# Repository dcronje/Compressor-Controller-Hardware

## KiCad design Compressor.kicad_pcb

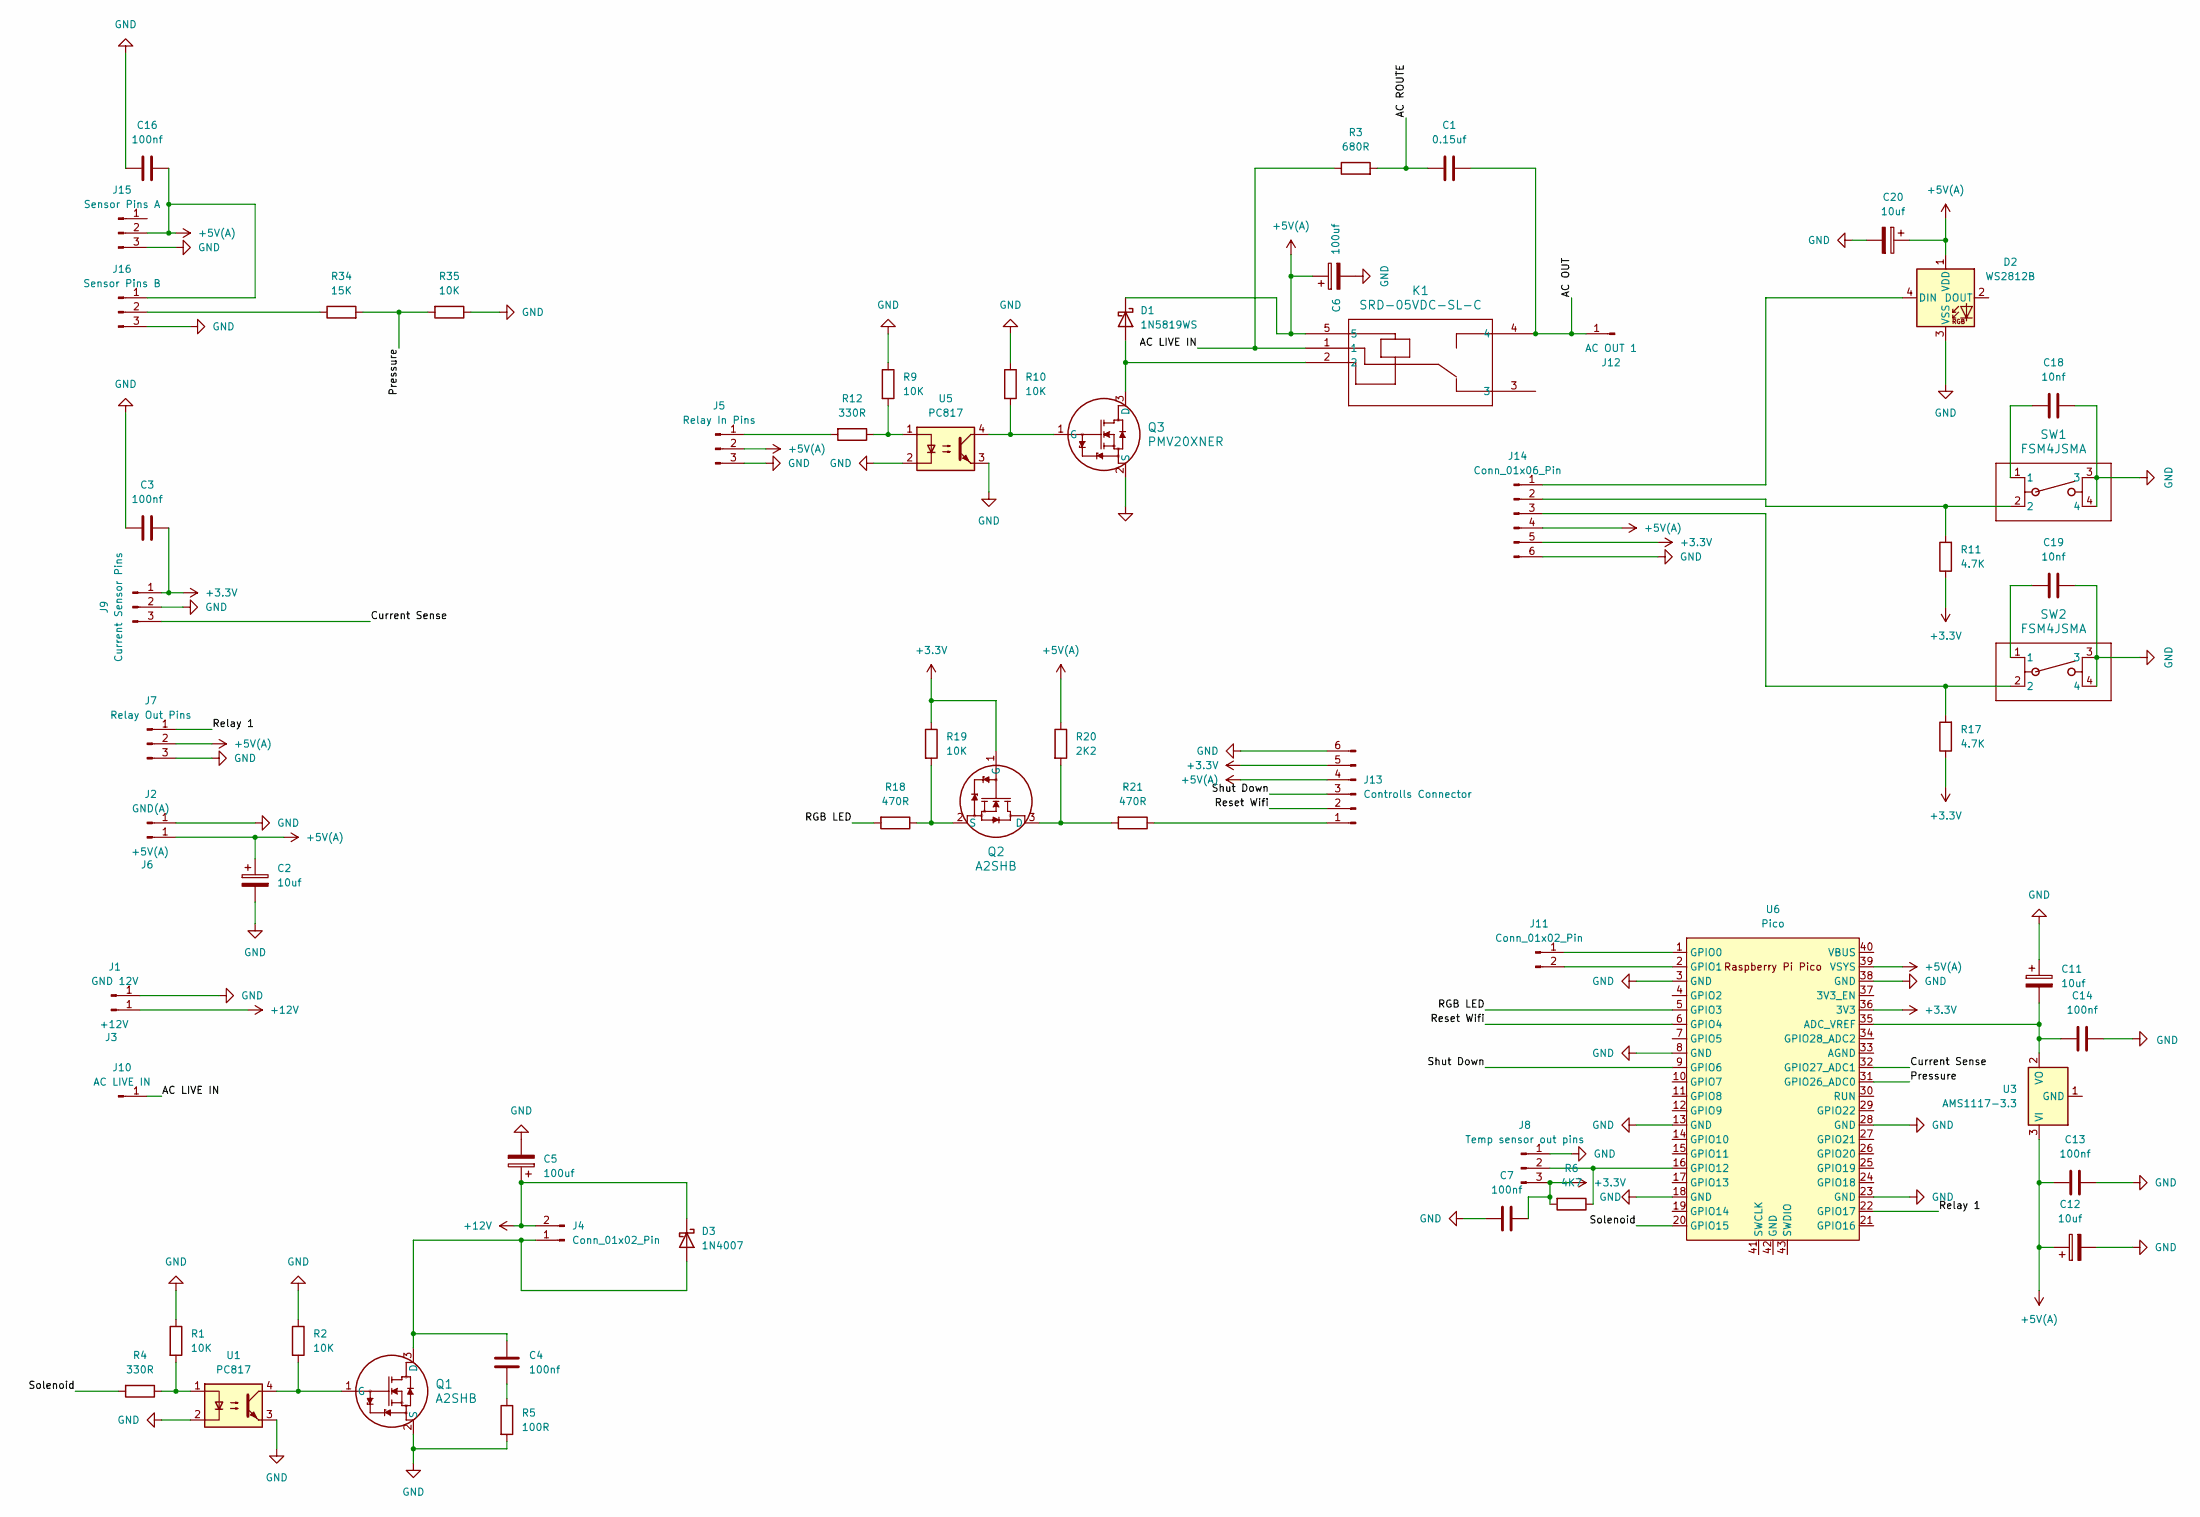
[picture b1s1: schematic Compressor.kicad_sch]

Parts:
C1: 0.15uf; C_Rect_L16.5mm_W7.0mm_P15.00mm_MKT
C2, C11, C12, C20: 10uf; CP_Elec_4x5.4
C3, C4, C7, C13, C14, C16: 100nf; C_1206_3216Metric_Pad1.33x1.80mm_HandSolder
C5, C6: 100uf; CP_Elec_10x10.5
C18, C19: 10nf; C_1206_3216Metric_Pad1.33x1.80mm_HandSolder
D1: 1N5819WS; D_SOD-323
D2: WS2812B; LED_WS2812B_PLCC4_5.0x5.0mm_P3.2mm
D3: 1N4007; D_SMA
J1: GND 12V; SolderWirePad_1x01_SMD_5x10mm
J2: GND(A); SolderWirePad_1x01_SMD_5x10mm
J3: +12V; SolderWirePad_1x01_SMD_5x10mm
J4, J11: Conn_01x02_Pin; SMD-PinHeader_1x02_P2.54mm_Vertical
J5: Relay In Pins; SMD-PinHeader_1x03_P2.54mm_Vertical
J6: +5V(A); SolderWirePad_1x01_SMD_5x10mm
J7: Relay Out Pins; SMD-PinHeader_1x03_P2.54mm_Vertical
J8: Temp sensor out pins; SMD-PinHeader_1x03_P2.54mm_Vertical
J9: Current Sensor Pins; SMD-PinHeader_1x03_P2.54mm_Vertical
J10: AC LIVE IN; SolderWirePad_1x01_SMD_5x10mm
J12: AC OUT 1; SolderWirePad_1x01_SMD_5x10mm
J13: Controlls Connector; SMD-PinHeader_1x06_P2.54mm_Vertical
J14: Conn_01x06_Pin; PinSocket_1x06_P2.54mm_Vertical
J15: Sensor Pins A; SMD-PinHeader_1x03_P2.54mm_Vertical
J16: Sensor Pins B; SMD-PinHeader_1x03_P2.54mm_Vertical
K1: SRD-05VDC-SL-C; RELAY_SRD-05VDC-SL-C_MCE
Q1, Q2: A2SHB; SOT23-TO-236AB_NEX
Q3: PMV20XNER; SOT23-TO-236AB_NEX
R1, R2, R9, R10, R19, R35: 10K; R_1206_3216Metric_Pad1.30x1.75mm_HandSolder
R3: 680R; R_Axial_Power_L25.0mm_W9.0mm_P30.48mm
R4, R12: 330R; R_1206_3216Metric_Pad1.30x1.75mm_HandSolder
R5: 100R; R_2512_6332Metric_Pad1.40x3.35mm_HandSolder
R6: 4K7; R_1206_3216Metric_Pad1.30x1.75mm_HandSolder
R11, R17: 4.7K; R_1206_3216Metric_Pad1.30x1.75mm_HandSolder
R18, R21: 470R; R_1206_3216Metric_Pad1.30x1.75mm_HandSolder
R20: 2K2; R_1206_3216Metric_Pad1.30x1.75mm_HandSolder
R34: 15K; R_1206_3216Metric_Pad1.30x1.75mm_HandSolder
SW1, SW2: FSM4JSMA; SW4_FSM4JSMA_TEC
U1, U5: PC817; SOP-4_4.4x2.6mm_P1.27mm
U3: AMS1117-3.3; SOT-223-3_TabPin2
U6: Pico; RPi_Pico_SMD

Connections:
+3.3V: C3.2, C7.2, J8.3, J9.1, J13.5, J14.5, Q2.1 (G), R6.2, R11.1, R17.1, R19.1, U6.36 (3V3)
+5V(A): C2.1, C6.1, C12.1, C13.1, C16.2, C20.1, D1.1 (K), D2.1 (VDD), J5.2, J6.1, J7.2, J13.4, J14.4, J15.2, J16.1, K1.5, R20.1, U3.3 (VI), U6.39 (VSYS)
+12V: C5.1, D3.1 (K), J3.1, J4.2
/AC LIVE IN: J10.1, K1.1, R3.1
/AC OUT: C1.2, J12.1, K1.4
/AC ROUTE: C1.1, R3.2
/Current Sense: J9.3, U6.32 (GPIO27_ADC1)
/Pressure: R34.2, R35.2, U6.31 (GPIO26_ADC0)
/RGB LED: R18.2, U6.5 (GPIO3)
/Relay 1: J7.1, U6.22 (GPIO17)
/Reset Wifi: J13.2, U6.6 (GPIO4)
/Shut Down: J13.3, U6.9 (GPIO6)
/Solenoid: R4.2, U6.20 (GPIO15)
GND: C2.2, C3.1, C5.2, C6.2, C7.1, C11.1, C12.2, C13.2, C14.2, C16.1, C18.2, C19.2, C20.2, D2.3 (VSS), J1.1, J2.1, J5.3, J7.3, J8.1, J9.2, J13.6, J14.6, J15.3, J16.3, Q1.2 (S), Q3.2 (S), R1.1, R2.1, R5.2, R9.1, R10.1, R35.1, SW1.3, SW1.4, SW2.3, SW2.4, U1.2, U1.3, U5.2, U5.3, U6.3 (GND), U6.8 (GND), U6.13 (GND), U6.18 (GND), U6.23 (GND), U6.28 (GND), U6.38 (GND)
unnamed: C4.2, R5.1
unnamed: C18.1, SW1.1
unnamed: C19.1, SW2.1
unnamed: D1.2 (A), K1.2, Q3.3 (D)
unnamed: D2.4 (DIN), J14.1
unnamed: C4.1, D3.2 (A), J4.1, Q1.3 (D)
unnamed: J5.1, R12.2
unnamed: J8.2, R6.1, U6.16 (GPIO12)
unnamed: J11.1, U6.1 (GPIO0)
unnamed: J11.2, U6.2 (GPIO1)
unnamed: J13.1, R21.1
unnamed: J14.2, R11.2, SW1.2
unnamed: J14.3, R17.2, SW2.2
unnamed: J16.2, R34.1
unnamed: Q1.1 (G), R2.2, U1.4
unnamed: Q2.3 (D), R20.2, R21.2
unnamed: Q2.2 (S), R18.1, R19.2
unnamed: Q3.1 (G), R10.2, U5.4
unnamed: R1.2, R4.1, U1.1
unnamed: R9.2, R12.1, U5.1
unnamed: C11.2, C14.1, U3.2 (VO), U6.35 (ADC_VREF)

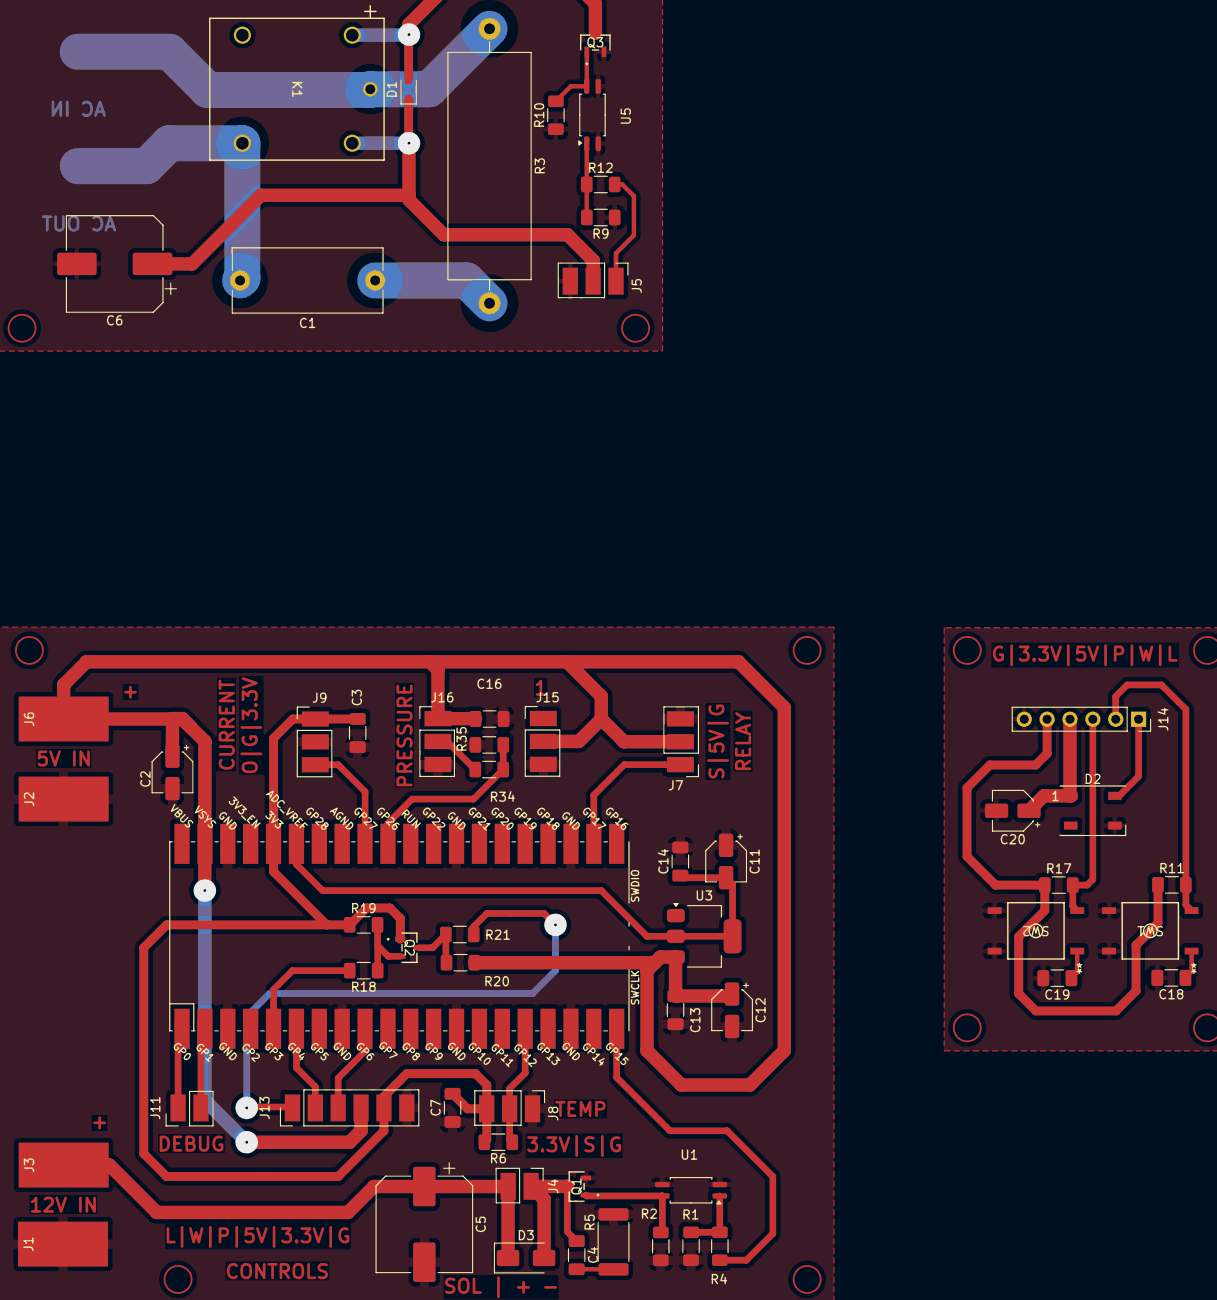
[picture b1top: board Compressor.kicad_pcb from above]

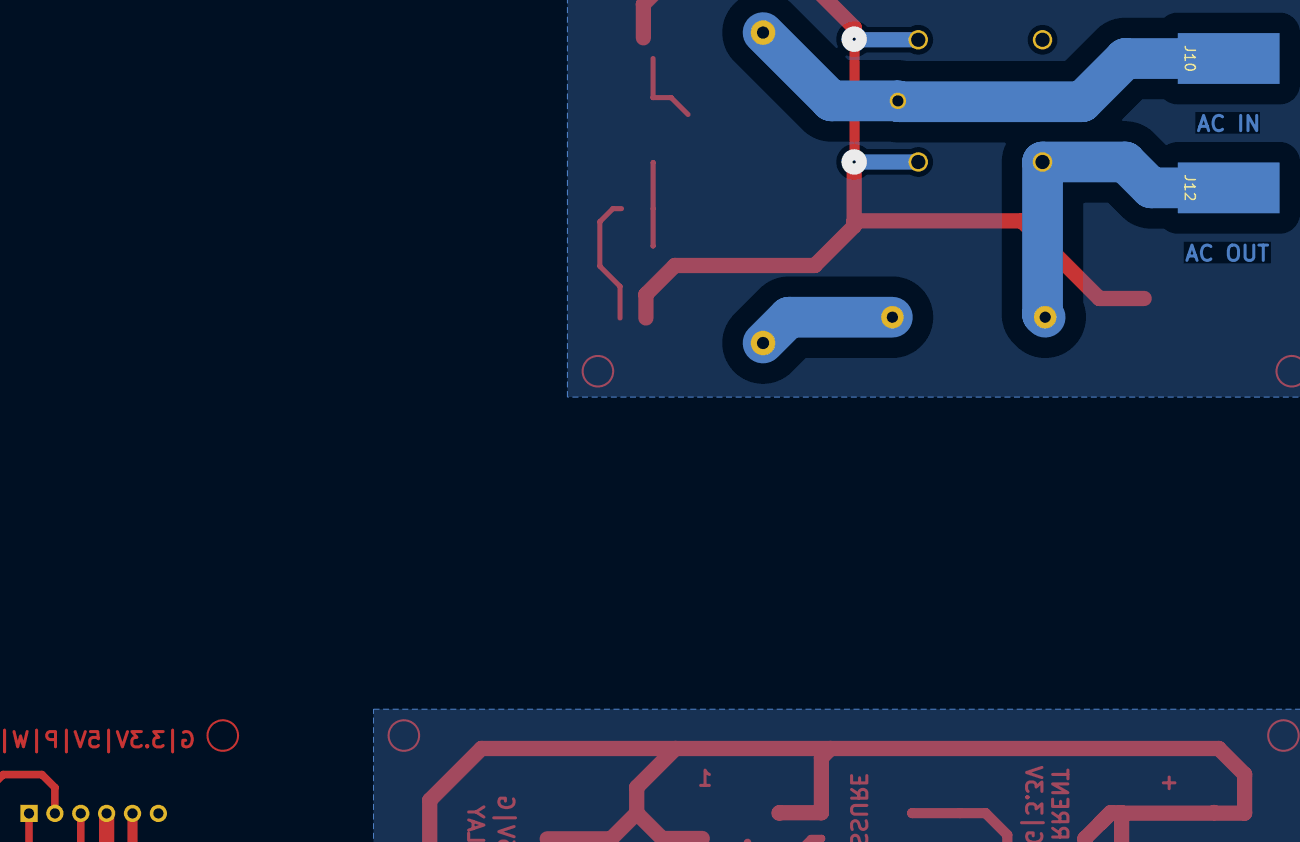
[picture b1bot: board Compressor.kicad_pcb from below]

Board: 2 copper layers, 61 parts (2 on the bottom side), 35 nets.

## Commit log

2025-01-23 Initial
2025-01-27 Split up boards
2025-02-01 Added temp sensor
